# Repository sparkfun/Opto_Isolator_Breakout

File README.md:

SparkFun Opto-isolator Breakout 
===============================

[*SparkFun Opto-isolator Breakout  (BOB-09118)*](https://www.sparkfun.com/products/9118)

This is a board designed for opto-isolation. 
This board is helpful for connecting digital systems (like a 5V microcontroller) to a high-voltage or noisy system. 
This board electrically isolates a controller from the high-power system by use of an opto-isolator IC.

Repository Contents
-------------------

* **/Hardware** - Eagle design files (.brd, .sch)
* **/Production** - Production panel files (.brd)

Documentation
--------------
* **[SparkFun Fritzing repo](https://github.com/sparkfun/Fritzing_Parts)** - Fritzing diagrams for SparkFun products.
* **[SparkFun 3D Model repo](https://github.com/sparkfun/3D_Models)** - 3D models of SparkFun products. 

License Information
-------------------

This product is _**open source**_! 

Please review the LICENSE.md file for license information. 

If you have any questions or concerns on licensing, please contact techsupport@sparkfun.com.

Distributed as-is; no warranty is given.

- Your friends at SparkFun.

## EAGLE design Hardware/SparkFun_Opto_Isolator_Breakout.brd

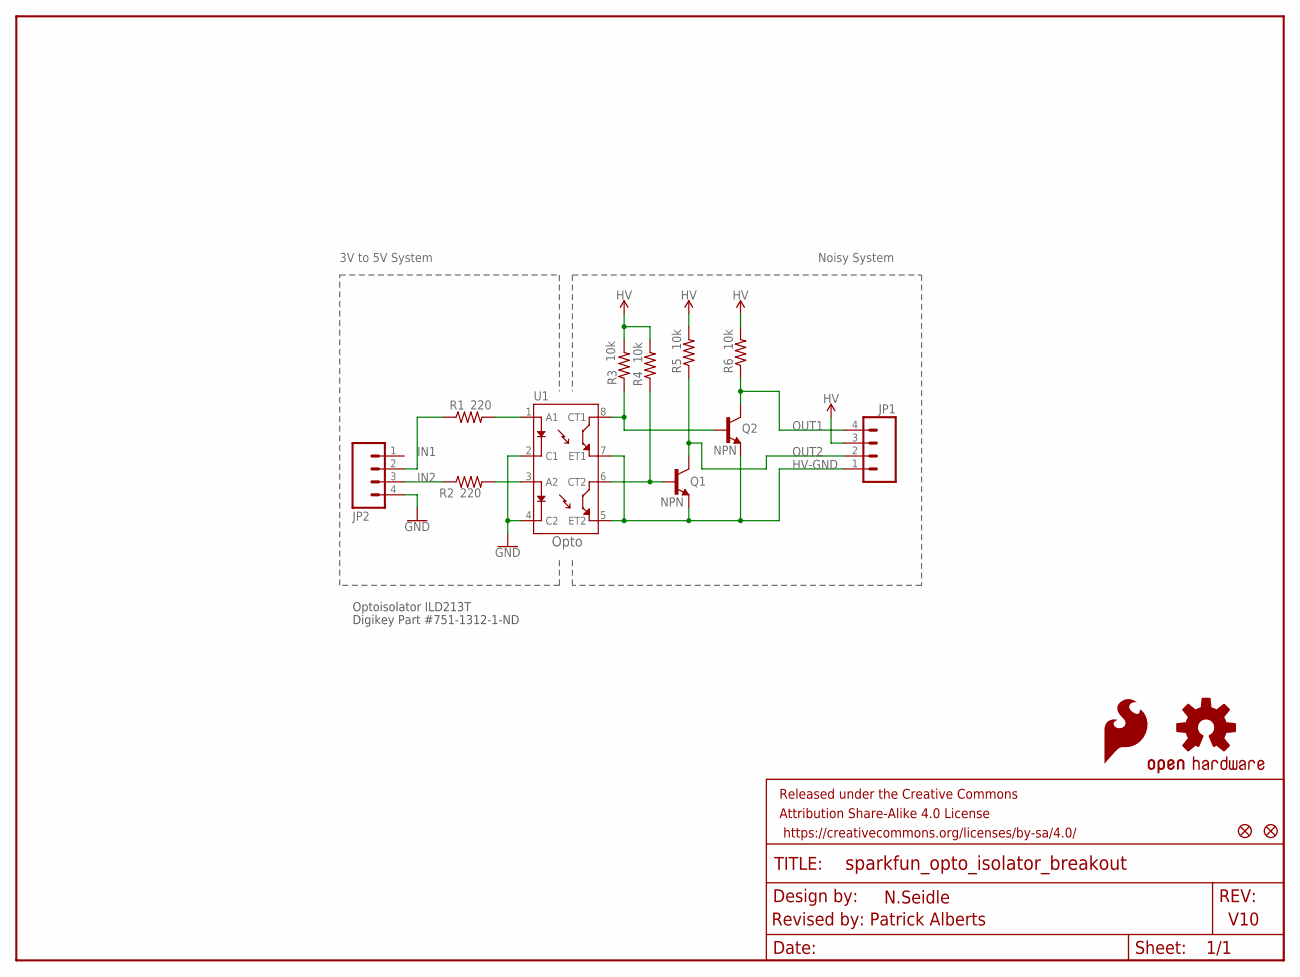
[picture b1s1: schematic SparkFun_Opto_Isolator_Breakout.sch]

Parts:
FRAME1: FRAME-LETTER; CREATIVE_COMMONS
JP1, JP2: M04PTH; 1X04
LOGO1: OSHW-LOGOS; OSHW-LOGO-S
LOGO2: SFE_LOGO_FLAME.1_INCH; SFE_LOGO_FLAME_.1
Q1, Q2: NPN; SOT23-3
R1, R2: 220; 0603
R3, R4, R5, R6: 10k; 0603
U1: ILD213T-IDL213T; SO08
U$2, U$3: FIDUCIALUFIDUCIAL; MICRO-FIDUCIAL

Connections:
GND: JP2.4, U1.2 (C1), U1.4 (C2)
HV-GND: JP1.1, Q1.2 (E), Q2.2 (E), U1.5 (ET2), U1.7 (ET1)
IN1: JP2.2, R1.1
IN2: JP2.3, R2.1
unnamed: R1.2, U1.1 (A1)
unnamed: R2.2, U1.3 (A2)
OUT1: JP1.4, Q2.3 (C), R6.1
OUT1N: Q2.1 (B), R3.1, U1.8 (CT1)
OUT2: JP1.2, Q1.3 (C), R5.1
OUT2N: Q1.1 (B), R4.1, U1.6 (CT2)
VCC: JP1.3, R3.2, R4.2, R5.2, R6.2

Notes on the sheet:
Optoisolator ILD213T
Digikey Part #751-1312-1-ND
3V to 5V System
Noisy System
V10
Revised by: Patrick Alberts
N.Seidle
Opto

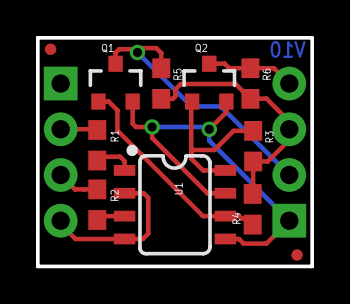
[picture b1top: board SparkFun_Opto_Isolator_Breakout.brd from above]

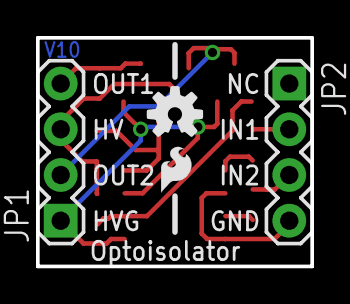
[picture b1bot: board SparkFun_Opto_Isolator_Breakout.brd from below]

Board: 2 copper layers, 15.2 x 12.7 mm, 16 parts (4 on the bottom side), 11 nets.

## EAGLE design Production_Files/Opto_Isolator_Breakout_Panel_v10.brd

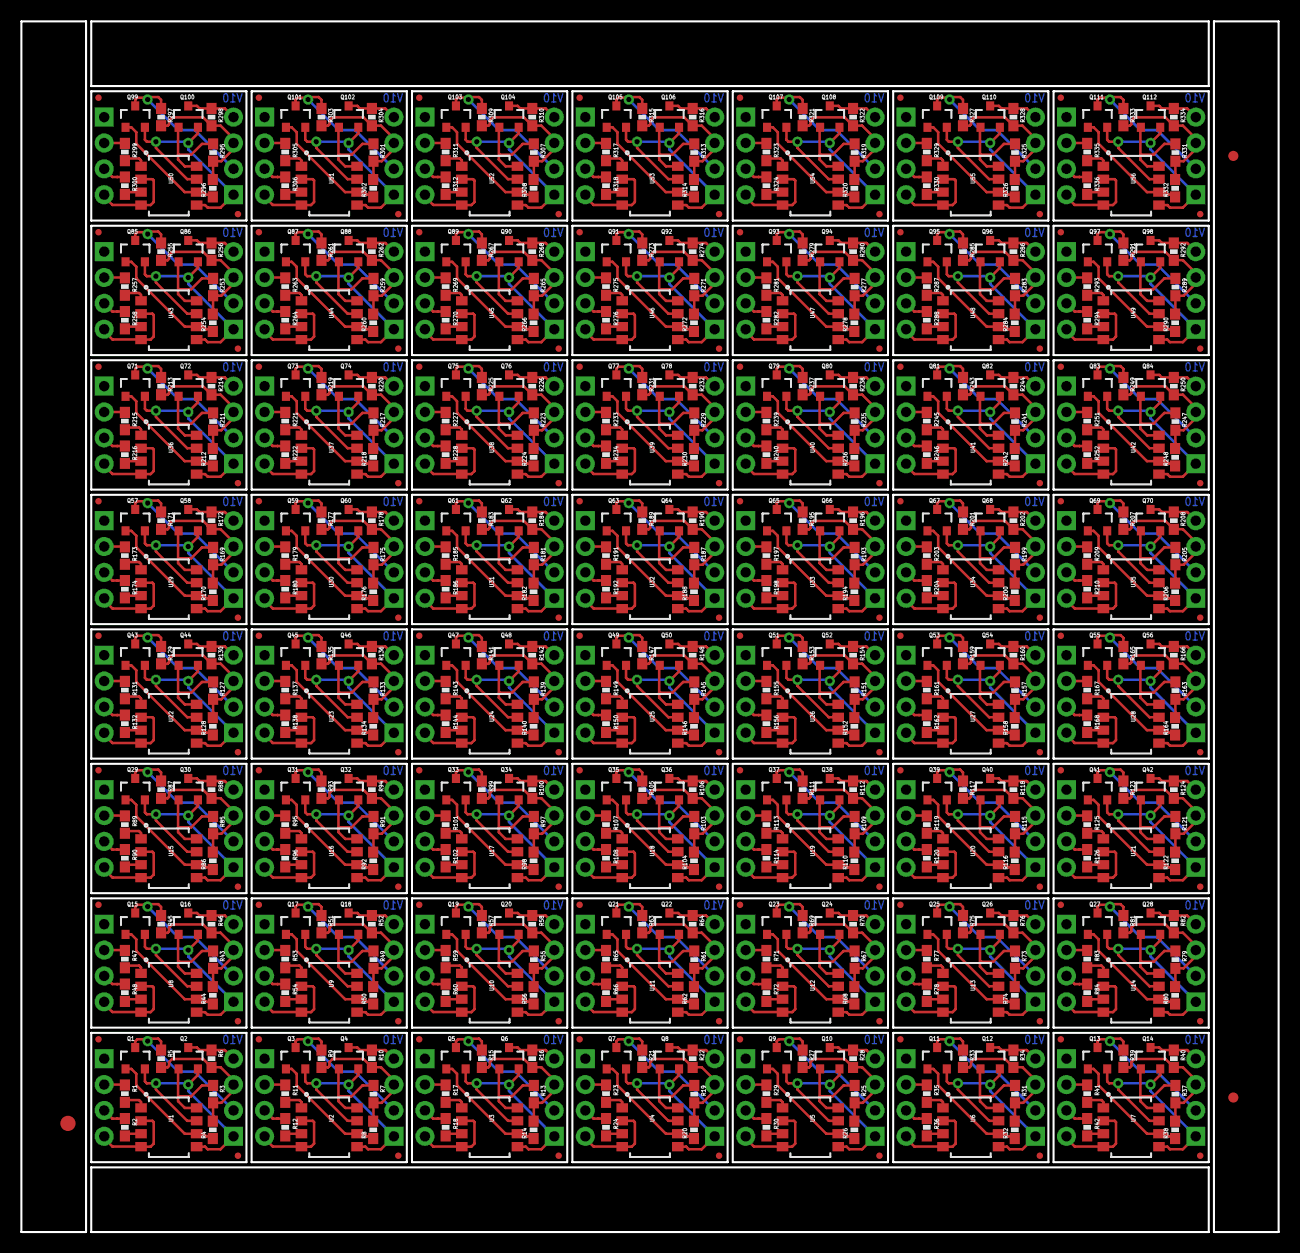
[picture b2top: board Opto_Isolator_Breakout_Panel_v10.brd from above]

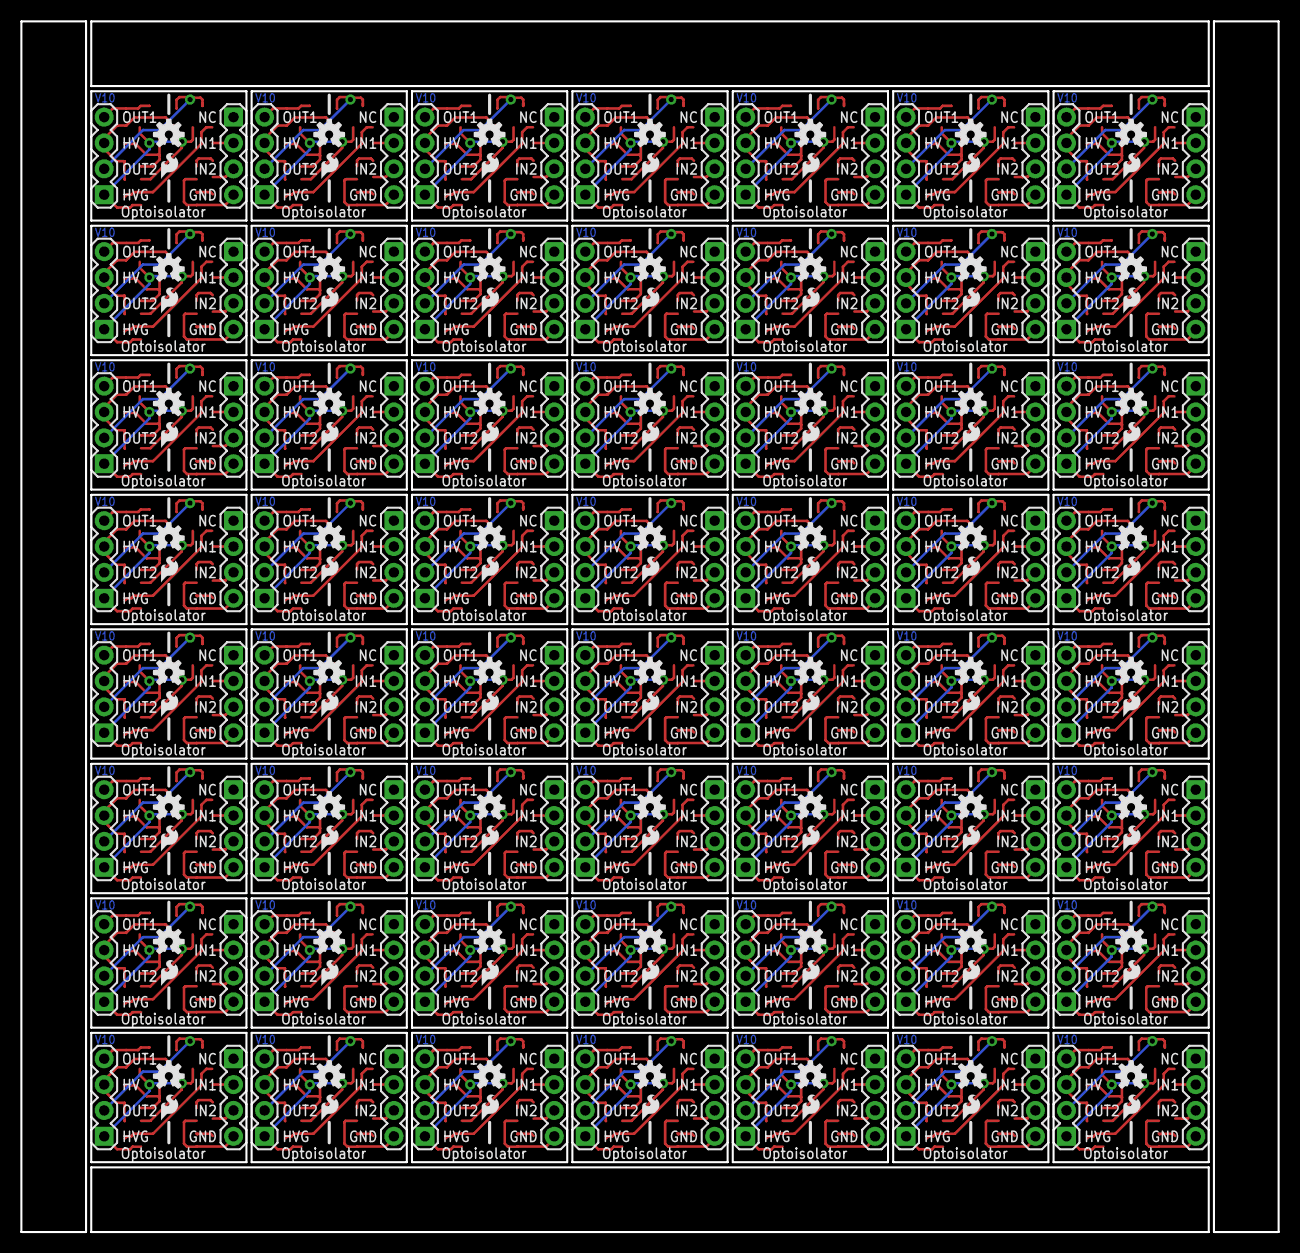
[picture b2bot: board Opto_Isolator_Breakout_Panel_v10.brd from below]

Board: 2 copper layers, 123.4 x 118.9 mm, 843 parts (224 on the bottom side), 616 nets.

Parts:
E$1: FIDUCIAL-1.5X3
E$4, E$5: FIDUCIAL-1X2
JP1, JP2, JP3, JP4, JP5, JP6, JP7, JP8, JP9, JP10, JP11, JP12, JP13, JP14, JP15, JP16, JP17, JP18, JP19, JP20, JP21, JP22, JP23, JP24, JP25, JP26, JP27, JP28, JP29, JP30, JP31, JP32, JP33, JP34, JP35, JP36, JP37, JP38, JP39, JP40, JP41, JP42, JP43, JP44, JP45, JP46, JP47, JP48, JP49, JP50, JP51, JP52, JP53, JP54, JP55, JP56, JP57, JP58, JP59, JP60, JP61, JP62, JP63, JP64, JP65, JP66, JP67, JP68, JP69, JP70, JP71, JP72, JP73, JP74, JP75, JP76, JP77, JP78, JP79, JP80, JP81, JP82, JP83, JP84, JP85, JP86, JP87, JP88, JP89, JP90, JP91, JP92, JP93, JP94, JP95, JP96, JP97, JP98, JP99, JP100, JP101, JP102, JP103, JP104, JP105, JP106, JP107, JP108, JP109, JP110, JP111, JP112: 1X04
LOGO1, LOGO4, LOGO6, LOGO8, LOGO10, LOGO12, LOGO14, LOGO16, LOGO18, LOGO20, LOGO22, LOGO24, LOGO26, LOGO28, LOGO30, LOGO32, LOGO34, LOGO36, LOGO38, LOGO40, LOGO42, LOGO44, LOGO46, LOGO48, LOGO50, LOGO52, LOGO54, LOGO56, LOGO58, LOGO60, LOGO62, LOGO64, LOGO66, LOGO68, LOGO70, LOGO72, LOGO74, LOGO76, LOGO78, LOGO80, LOGO82, LOGO84, LOGO86, LOGO88, LOGO90, LOGO92, LOGO94, LOGO96, LOGO98, LOGO100, LOGO102, LOGO104, LOGO106, LOGO108, LOGO110, LOGO112: OSHW-LOGOS; OSHW-LOGO-S
LOGO2, LOGO3, LOGO5, LOGO7, LOGO9, LOGO11, LOGO13, LOGO15, LOGO17, LOGO19, LOGO21, LOGO23, LOGO25, LOGO27, LOGO29, LOGO31, LOGO33, LOGO35, LOGO37, LOGO39, LOGO41, LOGO43, LOGO45, LOGO47, LOGO49, LOGO51, LOGO53, LOGO55, LOGO57, LOGO59, LOGO61, LOGO63, LOGO65, LOGO67, LOGO69, LOGO71, LOGO73, LOGO75, LOGO77, LOGO79, LOGO81, LOGO83, LOGO85, LOGO87, LOGO89, LOGO91, LOGO93, LOGO95, LOGO97, LOGO99, LOGO101, LOGO103, LOGO105, LOGO107, LOGO109, LOGO111: SFE_LOGO_FLAME.1_INCH; SFE_LOGO_FLAME_.1
Q1, Q2, Q3, Q4, Q5, Q6, Q7, Q8, Q9, Q10, Q11, Q12, Q13, Q14, Q15, Q16, Q17, Q18, Q19, Q20, Q21, Q22, Q23, Q24, Q25, Q26, Q27, Q28, Q29, Q30, Q31, Q32, Q33, Q34, Q35, Q36, Q37, Q38, Q39, Q40, Q41, Q42, Q43, Q44, Q45, Q46, Q47, Q48, Q49, Q50, Q51, Q52, Q53, Q54, Q55, Q56, Q57, Q58, Q59, Q60, Q61, Q62, Q63, Q64, Q65, Q66, Q67, Q68, Q69, Q70, Q71, Q72, Q73, Q74, Q75, Q76, Q77, Q78, Q79, Q80, Q81, Q82, Q83, Q84, Q85, Q86, Q87, Q88, Q89, Q90, Q91, Q92, Q93, Q94, Q95, Q96, Q97, Q98, Q99, Q100, Q101, Q102, Q103, Q104, Q105, Q106, Q107, Q108, Q109, Q110, Q111, Q112: NPN; SOT23-3
R1, R2, R11, R12, R17, R18, R23, R24, R29, R30, R35, R36, R41, R42, R47, R48, R53, R54, R59, R60, R65, R66, R71, R72, R77, R78, R83, R84, R89, R90, R95, R96, R101, R102, R107, R108, R113, R114, R119, R120, R125, R126, R131, R132, R137, R138, R143, R144, R149, R150, R155, R156, R161, R162, R167, R168, R173, R174, R179, R180, R185, R186, R191, R192, R197, R198, R203, R204, R209, R210, R215, R216, R221, R222, R227, R228, R233, R234, R239, R240, R245, R246, R251, R252, R257, R258, R263, R264, R269, R270, R275, R276, R281, R282, R287, R288, R293, R294, R299, R300, R305, R306, R311, R312, R317, R318, R323, R324, R329, R330, R335, R336: 220; 0603-RES
R3, R4, R5, R6, R7, R8, R9, R10, R13, R14, R15, R16, R19, R20, R21, R22, R25, R26, R27, R28, R31, R32, R33, R34, R37, R38, R39, R40, R43, R44, R45, R46, R49, R50, R51, R52, R55, R56, R57, R58, R61, R62, R63, R64, R67, R68, R69, R70, R73, R74, R75, R76, R79, R80, R81, R82, R85, R86, R87, R88, R91, R92, R93, R94, R97, R98, R99, R100, R103, R104, R105, R106, R109, R110, R111, R112, R115, R116, R117, R118, R121, R122, R123, R124, R127, R128, R129, R130, R133, R134, R135, R136, R139, R140, R141, R142, R145, R146, R147, R148, R151, R152, R153, R154, R157, R158, R159, R160, R163, R164, R165, R166, R169, R170, R171, R172, R175, R176, R177, R178, R181, R182, R183, R184, R187, R188, R189, R190, R193, R194, R195, R196, R199, R200, R201, R202, R205, R206, R207, R208, R211, R212, R213, R214, R217, R218, R219, R220, R223, R224, R225, R226, R229, R230, R231, R232, R235, R236, R237, R238, R241, R242, R243, R244, R247, R248, R249, R250, R253, R254, R255, R256, R259, R260, R261, R262, R265, R266, R267, R268, R271, R272, R273, R274, R277, R278, R279, R280, R283, R284, R285, R286, R289, R290, R291, R292, R295, R296, R297, R298, R301, R302, R303, R304, R307, R308, R309, R310, R313, R314, R315, R316, R319, R320, R321, R322, R325, R326, R327, R328, R331, R332, R333, R334: 10K; 0603-RES
U1, U2, U3, U4, U5, U6, U7, U8, U9, U10, U11, U12, U13, U14, U15, U16, U17, U18, U19, U20, U21, U22, U23, U24, U25, U26, U27, U28, U29, U30, U31, U32, U33, U34, U35, U36, U37, U38, U39, U40, U41, U42, U43, U44, U45, U46, U47, U48, U49, U50, U51, U52, U53, U54, U55, U56: OPTOISOLATOR-2SOIC8; SO08-2
U$1, U$2, U$3, U$4, U$5, U$6, U$7, U$8, U$9, U$10, U$11, U$12, U$13, U$14, U$15, U$16, U$17, U$18, U$19, U$20, U$21, U$22, U$23, U$24, U$25, U$26, U$27, U$28, U$29, U$30, U$31, U$32, U$33, U$34, U$35, U$36, U$37, U$38, U$39, U$40, U$41, U$42, U$43, U$44, U$45, U$46, U$47, U$48, U$49, U$50, U$51, U$52, U$53, U$54, U$55, U$56, U$57, U$58, U$59, U$60, U$61, U$62, U$63, U$64, U$65, U$66, U$67, U$68, U$69, U$70, U$71, U$72, U$73, U$74, U$75, U$76, U$77, U$78, U$79, U$80, U$81, U$82, U$83, U$84, U$85, U$86, U$87, U$88, U$89, U$90, U$91, U$92, U$93, U$94, U$95, U$96, U$97, U$98, U$99, U$100, U$101, U$102, U$103, U$104, U$105, U$106, U$107, U$108, U$109, U$110, U$111, U$112: FIDUCIALUFIDUCIAL; MICRO-FIDUCIAL

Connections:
GND: JP2.4, U1.2, U1.4
GND1: JP4.4, U2.2, U2.4
GND2: JP6.4, U3.2, U3.4
GND3: JP8.4, U4.2, U4.4
GND4: JP10.4, U5.2, U5.4
GND5: JP12.4, U6.2, U6.4
GND6: JP14.4, U7.2, U7.4
GND7: JP16.4, U8.2, U8.4
GND8: JP18.4, U9.2, U9.4
GND9: JP20.4, U10.2, U10.4
GND10: JP22.4, U11.2, U11.4
GND11: JP24.4, U12.2, U12.4
GND12: JP26.4, U13.2, U13.4
GND13: JP28.4, U14.2, U14.4
GND14: JP30.4, U15.2, U15.4
GND15: JP32.4, U16.2, U16.4
GND16: JP34.4, U17.2, U17.4
GND17: JP36.4, U18.2, U18.4
GND18: JP38.4, U19.2, U19.4
GND19: JP40.4, U20.2, U20.4
GND20: JP42.4, U21.2, U21.4
GND21: JP44.4, U22.2, U22.4
GND22: JP46.4, U23.2, U23.4
GND23: JP48.4, U24.2, U24.4
GND24: JP50.4, U25.2, U25.4
GND25: JP52.4, U26.2, U26.4
GND26: JP54.4, U27.2, U27.4
GND27: JP56.4, U28.2, U28.4
GND28: JP58.4, U29.2, U29.4
GND29: JP60.4, U30.2, U30.4
GND30: JP62.4, U31.2, U31.4
GND31: JP64.4, U32.2, U32.4
GND32: JP66.4, U33.2, U33.4
GND33: JP68.4, U34.2, U34.4
GND34: JP70.4, U35.2, U35.4
GND35: JP72.4, U36.2, U36.4
GND36: JP74.4, U37.2, U37.4
GND37: JP76.4, U38.2, U38.4
GND38: JP78.4, U39.2, U39.4
GND39: JP80.4, U40.2, U40.4
GND40: JP82.4, U41.2, U41.4
GND41: JP84.4, U42.2, U42.4
GND42: JP86.4, U43.2, U43.4
GND43: JP88.4, U44.2, U44.4
GND44: JP90.4, U45.2, U45.4
GND45: JP92.4, U46.2, U46.4
GND46: JP94.4, U47.2, U47.4
GND47: JP96.4, U48.2, U48.4
GND48: JP98.4, U49.2, U49.4
GND49: JP100.4, U50.2, U50.4
GND50: JP102.4, U51.2, U51.4
GND51: JP104.4, U52.2, U52.4
GND52: JP106.4, U53.2, U53.4
GND53: JP108.4, U54.2, U54.4
GND54: JP110.4, U55.2, U55.4
GND55: JP112.4, U56.2, U56.4
HV-GND: JP1.1, Q1.2, Q2.2, U1.5, U1.7
HV-GND1: JP3.1, Q3.2, Q4.2, U2.5, U2.7
HV-GND2: JP5.1, Q5.2, Q6.2, U3.5, U3.7
HV-GND3: JP7.1, Q7.2, Q8.2, U4.5, U4.7
HV-GND4: JP9.1, Q9.2, Q10.2, U5.5, U5.7
HV-GND5: JP11.1, Q11.2, Q12.2, U6.5, U6.7
HV-GND6: JP13.1, Q13.2, Q14.2, U7.5, U7.7
HV-GND7: JP15.1, Q15.2, Q16.2, U8.5, U8.7
HV-GND8: JP17.1, Q17.2, Q18.2, U9.5, U9.7
HV-GND9: JP19.1, Q19.2, Q20.2, U10.5, U10.7
HV-GND10: JP21.1, Q21.2, Q22.2, U11.5, U11.7
HV-GND11: JP23.1, Q23.2, Q24.2, U12.5, U12.7
HV-GND12: JP25.1, Q25.2, Q26.2, U13.5, U13.7
HV-GND13: JP27.1, Q27.2, Q28.2, U14.5, U14.7
HV-GND14: JP29.1, Q29.2, Q30.2, U15.5, U15.7
HV-GND15: JP31.1, Q31.2, Q32.2, U16.5, U16.7
HV-GND16: JP33.1, Q33.2, Q34.2, U17.5, U17.7
HV-GND17: JP35.1, Q35.2, Q36.2, U18.5, U18.7
HV-GND18: JP37.1, Q37.2, Q38.2, U19.5, U19.7
HV-GND19: JP39.1, Q39.2, Q40.2, U20.5, U20.7
HV-GND20: JP41.1, Q41.2, Q42.2, U21.5, U21.7
HV-GND21: JP43.1, Q43.2, Q44.2, U22.5, U22.7
HV-GND22: JP45.1, Q45.2, Q46.2, U23.5, U23.7
HV-GND23: JP47.1, Q47.2, Q48.2, U24.5, U24.7
HV-GND24: JP49.1, Q49.2, Q50.2, U25.5, U25.7
HV-GND25: JP51.1, Q51.2, Q52.2, U26.5, U26.7
HV-GND26: JP53.1, Q53.2, Q54.2, U27.5, U27.7
HV-GND27: JP55.1, Q55.2, Q56.2, U28.5, U28.7
HV-GND28: JP57.1, Q57.2, Q58.2, U29.5, U29.7
HV-GND29: JP59.1, Q59.2, Q60.2, U30.5, U30.7
HV-GND30: JP61.1, Q61.2, Q62.2, U31.5, U31.7
HV-GND31: JP63.1, Q63.2, Q64.2, U32.5, U32.7
HV-GND32: JP65.1, Q65.2, Q66.2, U33.5, U33.7
HV-GND33: JP67.1, Q67.2, Q68.2, U34.5, U34.7
HV-GND34: JP69.1, Q69.2, Q70.2, U35.5, U35.7
HV-GND35: JP71.1, Q71.2, Q72.2, U36.5, U36.7
HV-GND36: JP73.1, Q73.2, Q74.2, U37.5, U37.7
HV-GND37: JP75.1, Q75.2, Q76.2, U38.5, U38.7
HV-GND38: JP77.1, Q77.2, Q78.2, U39.5, U39.7
HV-GND39: JP79.1, Q79.2, Q80.2, U40.5, U40.7
HV-GND40: JP81.1, Q81.2, Q82.2, U41.5, U41.7
HV-GND41: JP83.1, Q83.2, Q84.2, U42.5, U42.7
HV-GND42: JP85.1, Q85.2, Q86.2, U43.5, U43.7
HV-GND43: JP87.1, Q87.2, Q88.2, U44.5, U44.7
HV-GND44: JP89.1, Q89.2, Q90.2, U45.5, U45.7
HV-GND45: JP91.1, Q91.2, Q92.2, U46.5, U46.7
HV-GND46: JP93.1, Q93.2, Q94.2, U47.5, U47.7
HV-GND47: JP95.1, Q95.2, Q96.2, U48.5, U48.7
HV-GND48: JP97.1, Q97.2, Q98.2, U49.5, U49.7
HV-GND49: JP99.1, Q99.2, Q100.2, U50.5, U50.7
HV-GND50: JP101.1, Q101.2, Q102.2, U51.5, U51.7
HV-GND51: JP103.1, Q103.2, Q104.2, U52.5, U52.7
HV-GND52: JP105.1, Q105.2, Q106.2, U53.5, U53.7
HV-GND53: JP107.1, Q107.2, Q108.2, U54.5, U54.7
HV-GND54: JP109.1, Q109.2, Q110.2, U55.5, U55.7
HV-GND55: JP111.1, Q111.2, Q112.2, U56.5, U56.7
IN1: JP2.2, R1.1
IN2: JP2.3, R2.1
IN3: JP4.3, R12.1
IN4: JP4.2, R11.1
IN5: JP6.3, R18.1
IN6: JP6.2, R17.1
IN7: JP8.3, R24.1
IN8: JP8.2, R23.1
IN9: JP10.3, R30.1
IN10: JP10.2, R29.1
IN11: JP12.3, R36.1
IN12: JP12.2, R35.1
IN13: JP14.3, R42.1
IN14: JP14.2, R41.1
IN15: JP16.3, R48.1
IN16: JP16.2, R47.1
IN17: JP18.3, R54.1
IN18: JP18.2, R53.1
IN19: JP20.3, R60.1
IN20: JP20.2, R59.1
IN21: JP22.3, R66.1
IN22: JP22.2, R65.1
IN23: JP24.3, R72.1
IN24: JP24.2, R71.1
IN25: JP26.3, R78.1
IN26: JP26.2, R77.1
IN27: JP28.3, R84.1
IN28: JP28.2, R83.1
IN29: JP30.3, R90.1
IN30: JP30.2, R89.1
IN31: JP32.3, R96.1
IN32: JP32.2, R95.1
IN33: JP34.3, R102.1
IN34: JP34.2, R101.1
IN35: JP36.3, R108.1
IN36: JP36.2, R107.1
IN37: JP38.3, R114.1
IN38: JP38.2, R113.1
IN39: JP40.3, R120.1
IN40: JP40.2, R119.1
IN41: JP42.3, R126.1
IN42: JP42.2, R125.1
IN43: JP44.3, R132.1
IN44: JP44.2, R131.1
IN45: JP46.3, R138.1
IN46: JP46.2, R137.1
IN47: JP48.3, R144.1
IN48: JP48.2, R143.1
IN49: JP50.3, R150.1
IN50: JP50.2, R149.1
IN51: JP52.3, R156.1
IN52: JP52.2, R155.1
IN53: JP54.3, R162.1
IN54: JP54.2, R161.1
IN55: JP56.3, R168.1
IN56: JP56.2, R167.1
IN57: JP58.3, R174.1
IN58: JP58.2, R173.1
IN59: JP60.3, R180.1
IN60: JP60.2, R179.1
IN61: JP62.3, R186.1
IN62: JP62.2, R185.1
IN63: JP64.3, R192.1
IN64: JP64.2, R191.1
IN65: JP66.3, R198.1
IN66: JP66.2, R197.1
IN67: JP68.3, R204.1
IN68: JP68.2, R203.1
IN69: JP70.3, R210.1
IN70: JP70.2, R209.1
IN71: JP72.3, R216.1
IN72: JP72.2, R215.1
IN73: JP74.3, R222.1
IN74: JP74.2, R221.1
IN75: JP76.3, R228.1
IN76: JP76.2, R227.1
IN77: JP78.3, R234.1
IN78: JP78.2, R233.1
IN79: JP80.3, R240.1
IN80: JP80.2, R239.1
IN81: JP82.3, R246.1
IN82: JP82.2, R245.1
IN83: JP84.3, R252.1
IN84: JP84.2, R251.1
IN85: JP86.3, R258.1
IN86: JP86.2, R257.1
IN87: JP88.3, R264.1
IN88: JP88.2, R263.1
IN89: JP90.3, R270.1
IN90: JP90.2, R269.1
IN91: JP92.3, R276.1
IN92: JP92.2, R275.1
IN93: JP94.3, R282.1
IN94: JP94.2, R281.1
IN95: JP96.3, R288.1
IN96: JP96.2, R287.1
IN97: JP98.3, R294.1
IN98: JP98.2, R293.1
IN99: JP100.3, R300.1
IN100: JP100.2, R299.1
IN101: JP102.3, R306.1
IN102: JP102.2, R305.1
IN103: JP104.3, R312.1
IN104: JP104.2, R311.1
IN105: JP106.3, R318.1
IN106: JP106.2, R317.1
IN107: JP108.3, R324.1
IN108: JP108.2, R323.1
IN109: JP110.3, R330.1
IN110: JP110.2, R329.1
IN111: JP112.3, R336.1
IN112: JP112.2, R335.1
unnamed: R1.2, U1.1
unnamed: R2.2, U1.3
unnamed: R11.2, U2.1
unnamed: R12.2, U2.3
unnamed: R17.2, U3.1
unnamed: R18.2, U3.3
unnamed: R23.2, U4.1
unnamed: R24.2, U4.3
unnamed: R29.2, U5.1
unnamed: R30.2, U5.3
unnamed: R35.2, U6.1
unnamed: R36.2, U6.3
unnamed: R41.2, U7.1
unnamed: R42.2, U7.3
unnamed: R47.2, U8.1
unnamed: R48.2, U8.3
unnamed: R53.2, U9.1
unnamed: R54.2, U9.3
unnamed: R59.2, U10.1
unnamed: R60.2, U10.3
unnamed: R65.2, U11.1
unnamed: R66.2, U11.3
unnamed: R71.2, U12.1
unnamed: R72.2, U12.3
unnamed: R77.2, U13.1
unnamed: R78.2, U13.3
unnamed: R83.2, U14.1
unnamed: R84.2, U14.3
unnamed: R89.2, U15.1
unnamed: R90.2, U15.3
unnamed: R95.2, U16.1
unnamed: R96.2, U16.3
unnamed: R101.2, U17.1
unnamed: R102.2, U17.3
unnamed: R107.2, U18.1
unnamed: R108.2, U18.3
unnamed: R113.2, U19.1
unnamed: R114.2, U19.3
unnamed: R119.2, U20.1
unnamed: R120.2, U20.3
unnamed: R125.2, U21.1
unnamed: R126.2, U21.3
unnamed: R131.2, U22.1
unnamed: R132.2, U22.3
unnamed: R137.2, U23.1
unnamed: R138.2, U23.3
unnamed: R143.2, U24.1
unnamed: R144.2, U24.3
unnamed: R149.2, U25.1
unnamed: R150.2, U25.3
unnamed: R155.2, U26.1
unnamed: R156.2, U26.3
unnamed: R161.2, U27.1
unnamed: R162.2, U27.3
unnamed: R167.2, U28.1
unnamed: R168.2, U28.3
unnamed: R173.2, U29.1
unnamed: R174.2, U29.3
unnamed: R179.2, U30.1
unnamed: R180.2, U30.3
unnamed: R185.2, U31.1
unnamed: R186.2, U31.3
unnamed: R191.2, U32.1
unnamed: R192.2, U32.3
unnamed: R197.2, U33.1
unnamed: R198.2, U33.3
unnamed: R203.2, U34.1
unnamed: R204.2, U34.3
unnamed: R209.2, U35.1
unnamed: R210.2, U35.3
unnamed: R215.2, U36.1
unnamed: R216.2, U36.3
unnamed: R221.2, U37.1
unnamed: R222.2, U37.3
unnamed: R227.2, U38.1
unnamed: R228.2, U38.3
unnamed: R233.2, U39.1
unnamed: R234.2, U39.3
unnamed: R239.2, U40.1
unnamed: R240.2, U40.3
unnamed: R245.2, U41.1
unnamed: R246.2, U41.3
unnamed: R251.2, U42.1
unnamed: R252.2, U42.3
unnamed: R257.2, U43.1
unnamed: R258.2, U43.3
unnamed: R263.2, U44.1
unnamed: R264.2, U44.3
unnamed: R269.2, U45.1
unnamed: R270.2, U45.3
unnamed: R275.2, U46.1
unnamed: R276.2, U46.3
unnamed: R281.2, U47.1
unnamed: R282.2, U47.3
unnamed: R287.2, U48.1
unnamed: R288.2, U48.3
unnamed: R293.2, U49.1
unnamed: R294.2, U49.3
unnamed: R299.2, U50.1
unnamed: R300.2, U50.3
unnamed: R305.2, U51.1
unnamed: R306.2, U51.3
unnamed: R311.2, U52.1
unnamed: R312.2, U52.3
unnamed: R317.2, U53.1
unnamed: R318.2, U53.3
unnamed: R323.2, U54.1
unnamed: R324.2, U54.3
unnamed: R329.2, U55.1
unnamed: R330.2, U55.3
unnamed: R335.2, U56.1
unnamed: R336.2, U56.3
OUT1: JP1.4, Q2.3, R6.1
OUT1N: Q2.1, R3.1, U1.8
OUT1N1: Q4.1, R7.1, U2.8
OUT1N2: Q6.1, R13.1, U3.8
OUT1N3: Q8.1, R19.1, U4.8
OUT1N4: Q10.1, R25.1, U5.8
OUT1N5: Q12.1, R31.1, U6.8
OUT1N6: Q14.1, R37.1, U7.8
OUT1N7: Q16.1, R43.1, U8.8
OUT1N8: Q18.1, R49.1, U9.8
OUT1N9: Q20.1, R55.1, U10.8
OUT1N10: Q22.1, R61.1, U11.8
OUT1N11: Q24.1, R67.1, U12.8
OUT1N12: Q26.1, R73.1, U13.8
OUT1N13: Q28.1, R79.1, U14.8
OUT1N14: Q30.1, R85.1, U15.8
OUT1N15: Q32.1, R91.1, U16.8
OUT1N16: Q34.1, R97.1, U17.8
OUT1N17: Q36.1, R103.1, U18.8
OUT1N18: Q38.1, R109.1, U19.8
OUT1N19: Q40.1, R115.1, U20.8
OUT1N20: Q42.1, R121.1, U21.8
OUT1N21: Q44.1, R127.1, U22.8
OUT1N22: Q46.1, R133.1, U23.8
OUT1N23: Q48.1, R139.1, U24.8
OUT1N24: Q50.1, R145.1, U25.8
OUT1N25: Q52.1, R151.1, U26.8
OUT1N26: Q54.1, R157.1, U27.8
OUT1N27: Q56.1, R163.1, U28.8
OUT1N28: Q58.1, R169.1, U29.8
OUT1N29: Q60.1, R175.1, U30.8
OUT1N30: Q62.1, R181.1, U31.8
OUT1N31: Q64.1, R187.1, U32.8
OUT1N32: Q66.1, R193.1, U33.8
OUT1N33: Q68.1, R199.1, U34.8
OUT1N34: Q70.1, R205.1, U35.8
OUT1N35: Q72.1, R211.1, U36.8
OUT1N36: Q74.1, R217.1, U37.8
OUT1N37: Q76.1, R223.1, U38.8
OUT1N38: Q78.1, R229.1, U39.8
OUT1N39: Q80.1, R235.1, U40.8
OUT1N40: Q82.1, R241.1, U41.8
OUT1N41: Q84.1, R247.1, U42.8
OUT1N42: Q86.1, R253.1, U43.8
OUT1N43: Q88.1, R259.1, U44.8
OUT1N44: Q90.1, R265.1, U45.8
OUT1N45: Q92.1, R271.1, U46.8
OUT1N46: Q94.1, R277.1, U47.8
OUT1N47: Q96.1, R283.1, U48.8
OUT1N48: Q98.1, R289.1, U49.8
OUT1N49: Q100.1, R295.1, U50.8
OUT1N50: Q102.1, R301.1, U51.8
OUT1N51: Q104.1, R307.1, U52.8
OUT1N52: Q106.1, R313.1, U53.8
OUT1N53: Q108.1, R319.1, U54.8
OUT1N54: Q110.1, R325.1, U55.8
OUT1N55: Q112.1, R331.1, U56.8
OUT2: JP1.2, Q1.3, R5.1
OUT2N: Q1.1, R4.1, U1.6
OUT2N1: Q3.1, R8.1, U2.6
OUT2N2: Q5.1, R14.1, U3.6
OUT2N3: Q7.1, R20.1, U4.6
OUT2N4: Q9.1, R26.1, U5.6
OUT2N5: Q11.1, R32.1, U6.6
OUT2N6: Q13.1, R38.1, U7.6
OUT2N7: Q15.1, R44.1, U8.6
OUT2N8: Q17.1, R50.1, U9.6
OUT2N9: Q19.1, R56.1, U10.6
OUT2N10: Q21.1, R62.1, U11.6
OUT2N11: Q23.1, R68.1, U12.6
OUT2N12: Q25.1, R74.1, U13.6
OUT2N13: Q27.1, R80.1, U14.6
OUT2N14: Q29.1, R86.1, U15.6
OUT2N15: Q31.1, R92.1, U16.6
OUT2N16: Q33.1, R98.1, U17.6
OUT2N17: Q35.1, R104.1, U18.6
OUT2N18: Q37.1, R110.1, U19.6
OUT2N19: Q39.1, R116.1, U20.6
OUT2N20: Q41.1, R122.1, U21.6
OUT2N21: Q43.1, R128.1, U22.6
OUT2N22: Q45.1, R134.1, U23.6
OUT2N23: Q47.1, R140.1, U24.6
OUT2N24: Q49.1, R146.1, U25.6
OUT2N25: Q51.1, R152.1, U26.6
OUT2N26: Q53.1, R158.1, U27.6
OUT2N27: Q55.1, R164.1, U28.6
OUT2N28: Q57.1, R170.1, U29.6
OUT2N29: Q59.1, R176.1, U30.6
OUT2N30: Q61.1, R182.1, U31.6
OUT2N31: Q63.1, R188.1, U32.6
OUT2N32: Q65.1, R194.1, U33.6
OUT2N33: Q67.1, R200.1, U34.6
OUT2N34: Q69.1, R206.1, U35.6
OUT2N35: Q71.1, R212.1, U36.6
OUT2N36: Q73.1, R218.1, U37.6
OUT2N37: Q75.1, R224.1, U38.6
OUT2N38: Q77.1, R230.1, U39.6
OUT2N39: Q79.1, R236.1, U40.6
OUT2N40: Q81.1, R242.1, U41.6
OUT2N41: Q83.1, R248.1, U42.6
OUT2N42: Q85.1, R254.1, U43.6
OUT2N43: Q87.1, R260.1, U44.6
OUT2N44: Q89.1, R266.1, U45.6
OUT2N45: Q91.1, R272.1, U46.6
OUT2N46: Q93.1, R278.1, U47.6
OUT2N47: Q95.1, R284.1, U48.6
OUT2N48: Q97.1, R290.1, U49.6
OUT2N49: Q99.1, R296.1, U50.6
OUT2N50: Q101.1, R302.1, U51.6
OUT2N51: Q103.1, R308.1, U52.6
OUT2N52: Q105.1, R314.1, U53.6
OUT2N53: Q107.1, R320.1, U54.6
OUT2N54: Q109.1, R326.1, U55.6
OUT2N55: Q111.1, R332.1, U56.6
OUT3: JP3.4, Q4.3, R10.1
OUT4: JP3.2, Q3.3, R9.1
OUT5: JP5.4, Q6.3, R16.1
OUT6: JP5.2, Q5.3, R15.1
OUT7: JP7.4, Q8.3, R22.1
OUT8: JP7.2, Q7.3, R21.1
OUT9: JP9.4, Q10.3, R28.1
OUT10: JP9.2, Q9.3, R27.1
OUT11: JP11.4, Q12.3, R34.1
OUT12: JP11.2, Q11.3, R33.1
OUT13: JP13.4, Q14.3, R40.1
OUT14: JP13.2, Q13.3, R39.1
OUT15: JP15.4, Q16.3, R46.1
OUT16: JP15.2, Q15.3, R45.1
OUT17: JP17.4, Q18.3, R52.1
OUT18: JP17.2, Q17.3, R51.1
OUT19: JP19.4, Q20.3, R58.1
OUT20: JP19.2, Q19.3, R57.1
OUT21: JP21.4, Q22.3, R64.1
OUT22: JP21.2, Q21.3, R63.1
OUT23: JP23.4, Q24.3, R70.1
OUT24: JP23.2, Q23.3, R69.1
OUT25: JP25.4, Q26.3, R76.1
OUT26: JP25.2, Q25.3, R75.1
OUT27: JP27.4, Q28.3, R82.1
OUT28: JP27.2, Q27.3, R81.1
OUT29: JP29.4, Q30.3, R88.1
OUT30: JP29.2, Q29.3, R87.1
OUT31: JP31.4, Q32.3, R94.1
OUT32: JP31.2, Q31.3, R93.1
OUT33: JP33.4, Q34.3, R100.1
OUT34: JP33.2, Q33.3, R99.1
OUT35: JP35.4, Q36.3, R106.1
OUT36: JP35.2, Q35.3, R105.1
OUT37: JP37.4, Q38.3, R112.1
OUT38: JP37.2, Q37.3, R111.1
OUT39: JP39.4, Q40.3, R118.1
OUT40: JP39.2, Q39.3, R117.1
OUT41: JP41.4, Q42.3, R124.1
OUT42: JP41.2, Q41.3, R123.1
OUT43: JP43.4, Q44.3, R130.1
OUT44: JP43.2, Q43.3, R129.1
OUT45: JP45.4, Q46.3, R136.1
OUT46: JP45.2, Q45.3, R135.1
OUT47: JP47.4, Q48.3, R142.1
OUT48: JP47.2, Q47.3, R141.1
OUT49: JP49.4, Q50.3, R148.1
OUT50: JP49.2, Q49.3, R147.1
OUT51: JP51.4, Q52.3, R154.1
OUT52: JP51.2, Q51.3, R153.1
OUT53: JP53.4, Q54.3, R160.1
OUT54: JP53.2, Q53.3, R159.1
OUT55: JP55.4, Q56.3, R166.1
OUT56: JP55.2, Q55.3, R165.1
OUT57: JP57.4, Q58.3, R172.1
OUT58: JP57.2, Q57.3, R171.1
OUT59: JP59.4, Q60.3, R178.1
OUT60: JP59.2, Q59.3, R177.1
OUT61: JP61.4, Q62.3, R184.1
OUT62: JP61.2, Q61.3, R183.1
OUT63: JP63.4, Q64.3, R190.1
OUT64: JP63.2, Q63.3, R189.1
OUT65: JP65.4, Q66.3, R196.1
OUT66: JP65.2, Q65.3, R195.1
OUT67: JP67.4, Q68.3, R202.1
OUT68: JP67.2, Q67.3, R201.1
OUT69: JP69.4, Q70.3, R208.1
OUT70: JP69.2, Q69.3, R207.1
OUT71: JP71.4, Q72.3, R214.1
OUT72: JP71.2, Q71.3, R213.1
OUT73: JP73.4, Q74.3, R220.1
OUT74: JP73.2, Q73.3, R219.1
OUT75: JP75.4, Q76.3, R226.1
OUT76: JP75.2, Q75.3, R225.1
OUT77: JP77.4, Q78.3, R232.1
OUT78: JP77.2, Q77.3, R231.1
OUT79: JP79.4, Q80.3, R238.1
OUT80: JP79.2, Q79.3, R237.1
OUT81: JP81.4, Q82.3, R244.1
OUT82: JP81.2, Q81.3, R243.1
OUT83: JP83.4, Q84.3, R250.1
OUT84: JP83.2, Q83.3, R249.1
OUT85: JP85.4, Q86.3, R256.1
OUT86: JP85.2, Q85.3, R255.1
OUT87: JP87.4, Q88.3, R262.1
OUT88: JP87.2, Q87.3, R261.1
OUT89: JP89.4, Q90.3, R268.1
OUT90: JP89.2, Q89.3, R267.1
OUT91: JP91.4, Q92.3, R274.1
OUT92: JP91.2, Q91.3, R273.1
OUT93: JP93.4, Q94.3, R280.1
OUT94: JP93.2, Q93.3, R279.1
OUT95: JP95.4, Q96.3, R286.1
OUT96: JP95.2, Q95.3, R285.1
OUT97: JP97.4, Q98.3, R292.1
OUT98: JP97.2, Q97.3, R291.1
OUT99: JP99.4, Q100.3, R298.1
OUT100: JP99.2, Q99.3, R297.1
OUT101: JP101.4, Q102.3, R304.1
OUT102: JP101.2, Q101.3, R303.1
OUT103: JP103.4, Q104.3, R310.1
OUT104: JP103.2, Q103.3, R309.1
OUT105: JP105.4, Q106.3, R316.1
OUT106: JP105.2, Q105.3, R315.1
OUT107: JP107.4, Q108.3, R322.1
OUT108: JP107.2, Q107.3, R321.1
OUT109: JP109.4, Q110.3, R328.1
OUT110: JP109.2, Q109.3, R327.1
OUT111: JP111.4, Q112.3, R334.1
OUT112: JP111.2, Q111.3, R333.1
VCC: JP1.3, R3.2, R4.2, R5.2, R6.2
VCC1: JP3.3, R7.2, R8.2, R9.2, R10.2
VCC2: JP5.3, R13.2, R14.2, R15.2, R16.2
VCC3: JP7.3, R19.2, R20.2, R21.2, R22.2
VCC4: JP9.3, R25.2, R26.2, R27.2, R28.2
VCC5: JP11.3, R31.2, R32.2, R33.2, R34.2
VCC6: JP13.3, R37.2, R38.2, R39.2, R40.2
VCC7: JP15.3, R43.2, R44.2, R45.2, R46.2
VCC8: JP17.3, R49.2, R50.2, R51.2, R52.2
VCC9: JP19.3, R55.2, R56.2, R57.2, R58.2
VCC10: JP21.3, R61.2, R62.2, R63.2, R64.2
VCC11: JP23.3, R67.2, R68.2, R69.2, R70.2
VCC12: JP25.3, R73.2, R74.2, R75.2, R76.2
VCC13: JP27.3, R79.2, R80.2, R81.2, R82.2
VCC14: JP29.3, R85.2, R86.2, R87.2, R88.2
VCC15: JP31.3, R91.2, R92.2, R93.2, R94.2
VCC16: JP33.3, R97.2, R98.2, R99.2, R100.2
VCC17: JP35.3, R103.2, R104.2, R105.2, R106.2
VCC18: JP37.3, R109.2, R110.2, R111.2, R112.2
VCC19: JP39.3, R115.2, R116.2, R117.2, R118.2
VCC20: JP41.3, R121.2, R122.2, R123.2, R124.2
VCC21: JP43.3, R127.2, R128.2, R129.2, R130.2
VCC22: JP45.3, R133.2, R134.2, R135.2, R136.2
VCC23: JP47.3, R139.2, R140.2, R141.2, R142.2
VCC24: JP49.3, R145.2, R146.2, R147.2, R148.2
VCC25: JP51.3, R151.2, R152.2, R153.2, R154.2
VCC26: JP53.3, R157.2, R158.2, R159.2, R160.2
VCC27: JP55.3, R163.2, R164.2, R165.2, R166.2
VCC28: JP57.3, R169.2, R170.2, R171.2, R172.2
VCC29: JP59.3, R175.2, R176.2, R177.2, R178.2
VCC30: JP61.3, R181.2, R182.2, R183.2, R184.2
VCC31: JP63.3, R187.2, R188.2, R189.2, R190.2
VCC32: JP65.3, R193.2, R194.2, R195.2, R196.2
VCC33: JP67.3, R199.2, R200.2, R201.2, R202.2
VCC34: JP69.3, R205.2, R206.2, R207.2, R208.2
VCC35: JP71.3, R211.2, R212.2, R213.2, R214.2
VCC36: JP73.3, R217.2, R218.2, R219.2, R220.2
VCC37: JP75.3, R223.2, R224.2, R225.2, R226.2
VCC38: JP77.3, R229.2, R230.2, R231.2, R232.2
VCC39: JP79.3, R235.2, R236.2, R237.2, R238.2
VCC40: JP81.3, R241.2, R242.2, R243.2, R244.2
VCC41: JP83.3, R247.2, R248.2, R249.2, R250.2
VCC42: JP85.3, R253.2, R254.2, R255.2, R256.2
VCC43: JP87.3, R259.2, R260.2, R261.2, R262.2
VCC44: JP89.3, R265.2, R266.2, R267.2, R268.2
VCC45: JP91.3, R271.2, R272.2, R273.2, R274.2
VCC46: JP93.3, R277.2, R278.2, R279.2, R280.2
VCC47: JP95.3, R283.2, R284.2, R285.2, R286.2
VCC48: JP97.3, R289.2, R290.2, R291.2, R292.2
VCC49: JP99.3, R295.2, R296.2, R297.2, R298.2
VCC50: JP101.3, R301.2, R302.2, R303.2, R304.2
VCC51: JP103.3, R307.2, R308.2, R309.2, R310.2
VCC52: JP105.3, R313.2, R314.2, R315.2, R316.2
VCC53: JP107.3, R319.2, R320.2, R321.2, R322.2
VCC54: JP109.3, R325.2, R326.2, R327.2, R328.2
VCC55: JP111.3, R331.2, R332.2, R333.2, R334.2

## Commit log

2014-10-29 initial commit with brd/sch
2014-10-29 0603, sch changes, re routes, oshw and headers
    Update all res/caps to 0603
    minor trace re routes
    oshw added and sch frame update to letter
    moved feducials to micro
    updated headers to have correct annual ring size
2014-11-06 Changed Res Values / SCH cleanup
    changed r1 and r2 to 200K
    Added version # and eng to board/sch files
2015-01-14 Computer change
2015-03-26 Added attributes for IC IDL213T
2015-03-31 Fixed qc checklist issues.
2015-03-31 Fixed final qc checklist items.
2015-04-20 Fixed QC checklist issues
    Fixed version # in sch and brd
    added "all units in inches" in layer 47
2015-04-23 created panel v10
2015-09-01 Adding license and .git files, updating README with product info
2021-07-06 Replace ILD213T with updated part

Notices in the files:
parts and their libraries:
SparkFun-Connectors: Licensing: Creative Commons ShareAlike 4.0 International - https://creativecommons.org/licenses/by-sa/4.0
SparkFun-Aesthetics: Released under the Creative Commons Attribution Share-Alike 4.0 License
SparkFun-Aesthetics: https://creativecommons.org/licenses/by-sa/4.0
